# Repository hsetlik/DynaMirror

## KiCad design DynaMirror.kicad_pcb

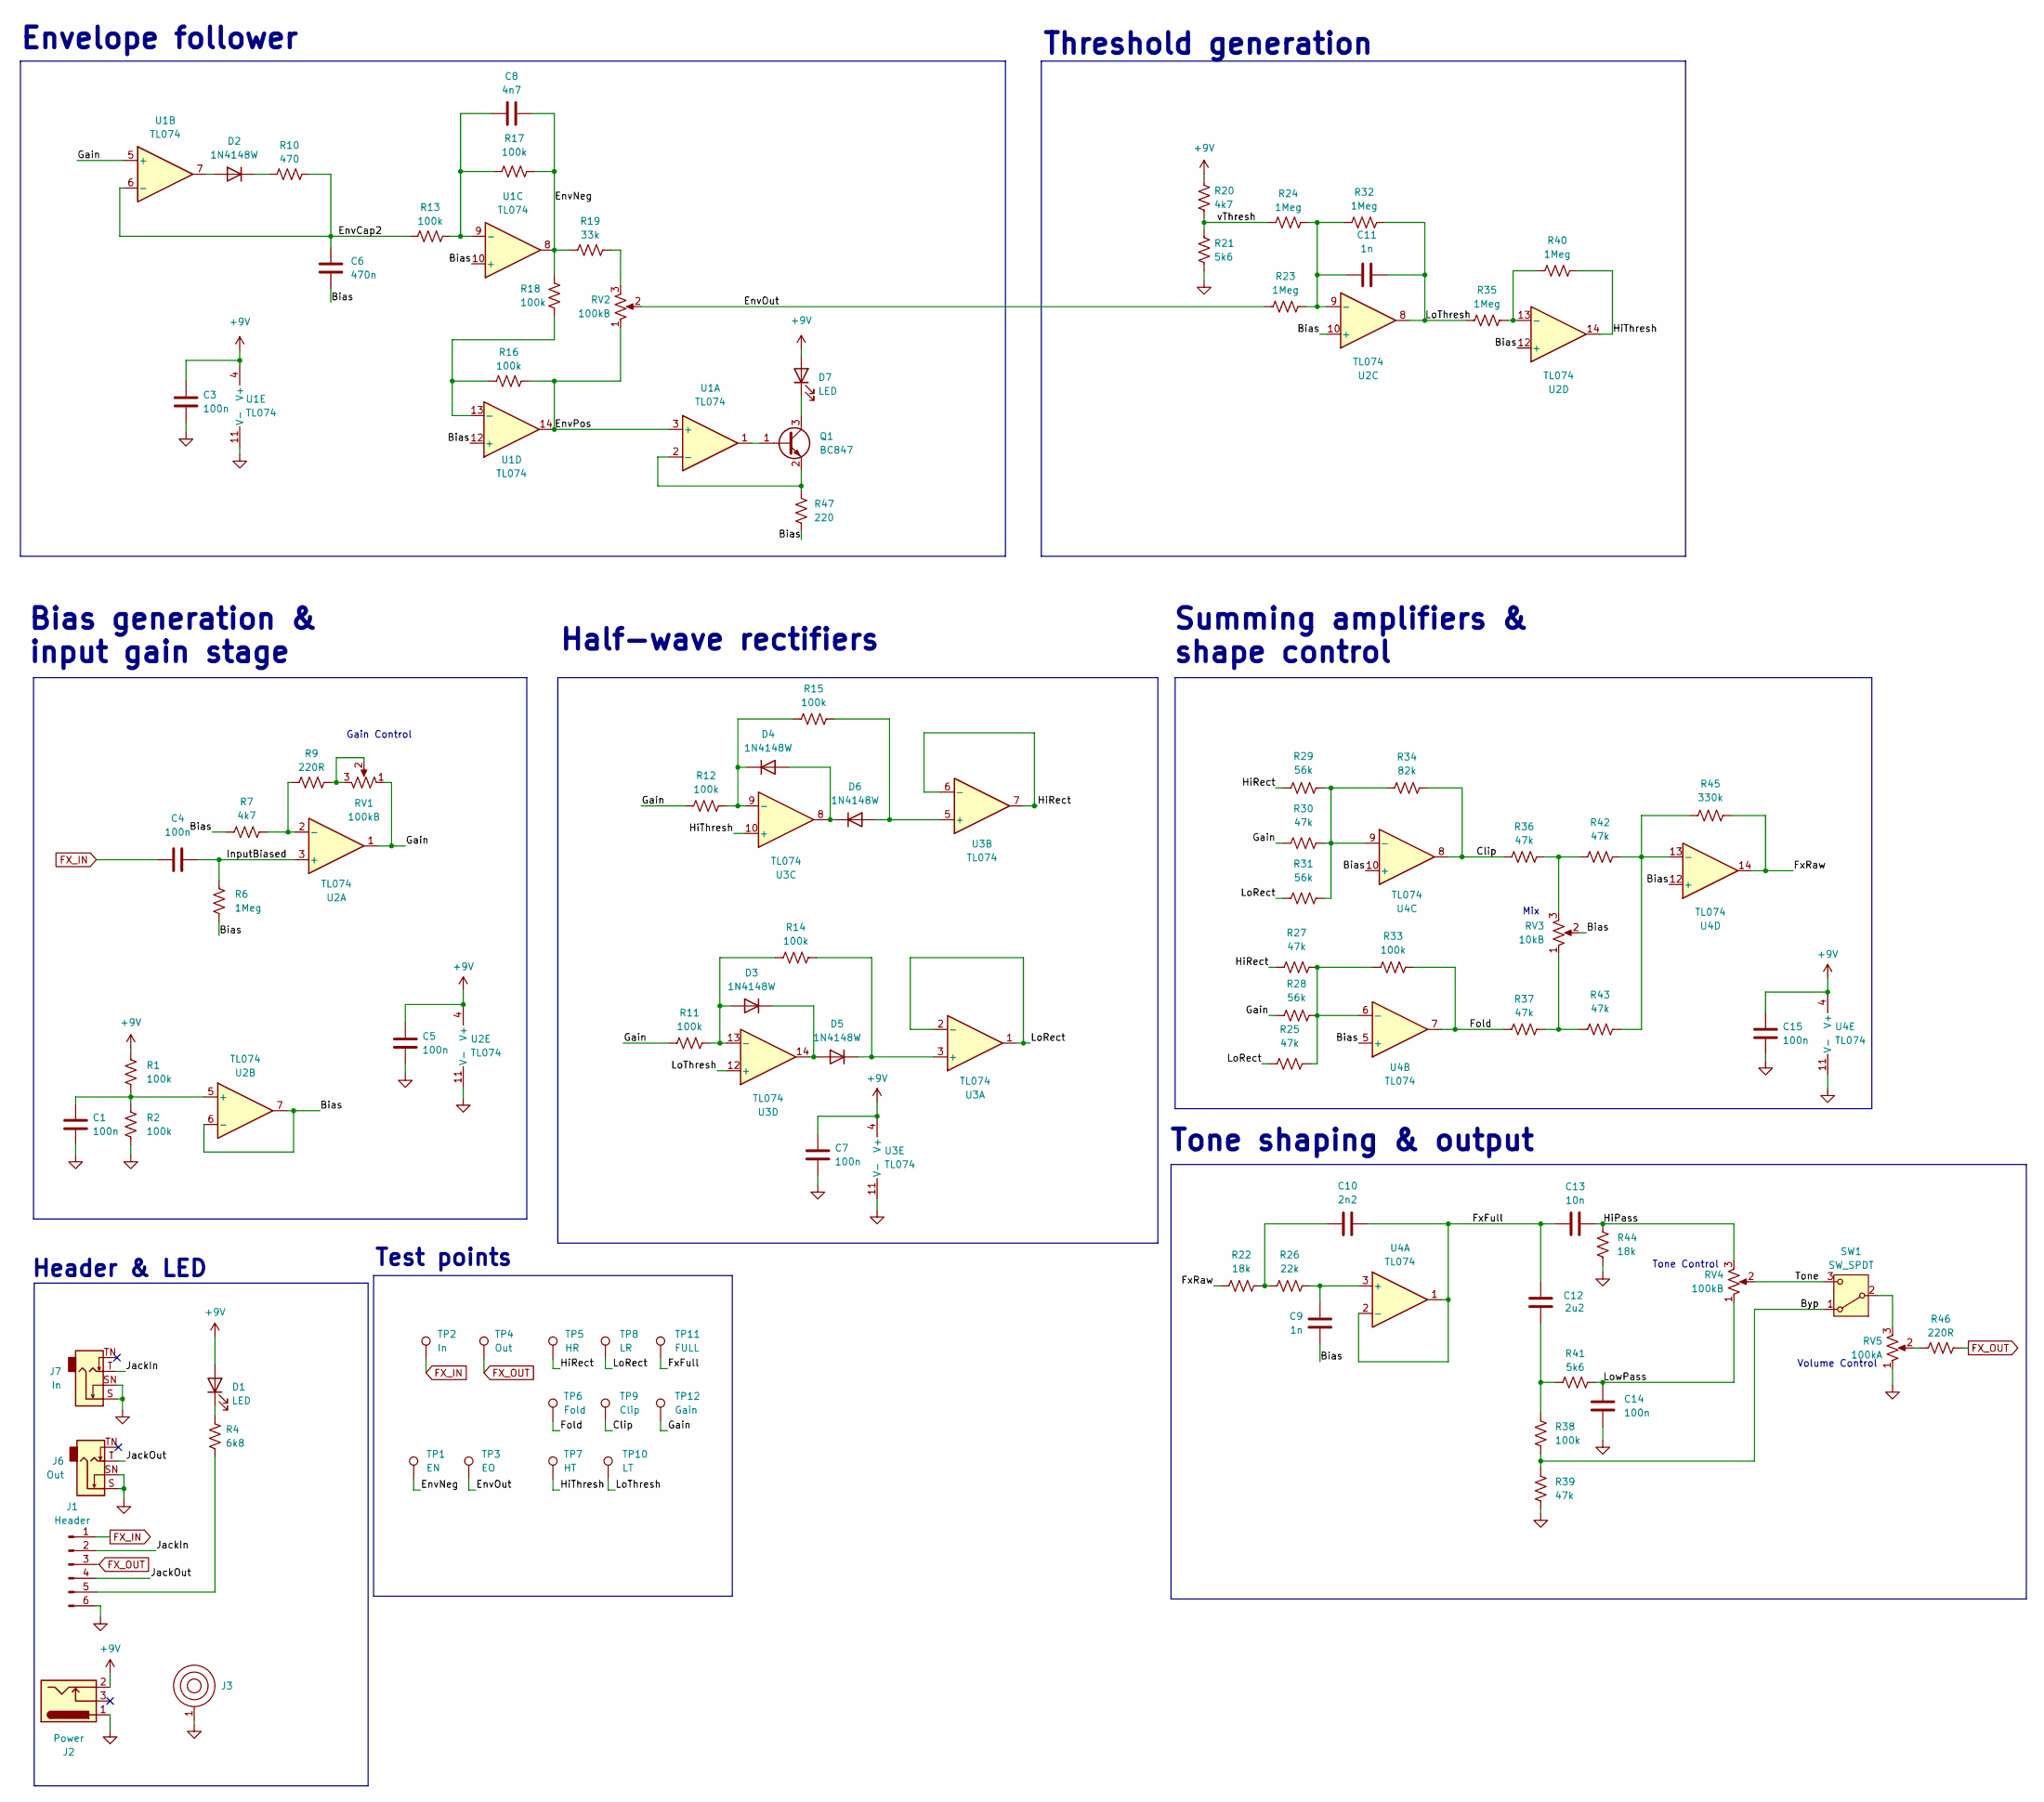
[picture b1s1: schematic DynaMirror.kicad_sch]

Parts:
C1, C3, C4, C5, C7, C14, C15: 100n; C_0805_2012Metric
C6: 470n; C_0805_2012Metric
C8: 4n7; C_0805_2012Metric
C9, C11: 1n; C_0805_2012Metric
C10: 2n2; C_0805_2012Metric
C12: 2u2; C_0805_2012Metric
C13: 10n; C_0805_2012Metric
D1, D7: LED; LED_D3.0mm
D2, D3, D4, D5, D6: 1N4148W; D_SOD-123
J1: Header; PinHeader_1x06_P2.54mm_Vertical
J2: Power; BarrelJack_Horizontal
J3: BatteryContact_Keystone_243
J6: Out; Jack_6.35mm_Tayda_PJ664C_Mono_Horizontal; MPN PJ-644C MONO
J7: In; Jack_6.35mm_Tayda_PJ664C_Mono_Horizontal; MPN PJ-644C MONO
Q1: BC847; SOT-23
R1, R2, R11, R12, R13, R14, R15, R16, R17, R18, R33, R38: 100k; R_0805_2012Metric
R4: 6k8; R_0805_2012Metric
R6, R23, R24, R32, R35, R40: 1Meg; R_0805_2012Metric
R7, R20: 4k7; R_0805_2012Metric
R9, R46: 220R; R_0805_2012Metric
R10: 470; R_0805_2012Metric
R19: 33k; R_0805_2012Metric
R21, R41: 5k6; R_0805_2012Metric
R22, R44: 18k; R_0805_2012Metric
R25, R27, R30, R36, R37, R39, R42, R43: 47k; R_0805_2012Metric
R26: 22k; R_0805_2012Metric
R28, R29, R31: 56k; R_0805_2012Metric
R34: 82k; R_0805_2012Metric
R45: 330k; R_0805_2012Metric
R47: 220; R_0805_2012Metric
RV1, RV2, RV4: 100kB; Potentiometer_Alpha_RV16AF_42_VeryLong
RV3: 10kB; Potentiometer_Alpha_RV16AF_42_VeryLong
RV5: 100kA; Potentiometer_Alpha_RV16AF_42_VeryLong
SW1: SW_SPDT; SW_SPDT_Dailywell_Mini_1M
TP1: EN; TestPoint_THTPad_D2.0mm_Drill1.0mm_VAL
TP2: In; TestPoint_THTPad_D2.0mm_Drill1.0mm_VAL
TP3: EO; TestPoint_THTPad_D2.0mm_Drill1.0mm_VAL
TP4: Out; TestPoint_THTPad_D2.0mm_Drill1.0mm_VAL
TP5: HR; TestPoint_THTPad_D2.0mm_Drill1.0mm_VAL
TP6: Fold; TestPoint_THTPad_D2.0mm_Drill1.0mm_VAL
TP7: HT; TestPoint_THTPad_D2.0mm_Drill1.0mm_VAL
TP8: LR; TestPoint_THTPad_D2.0mm_Drill1.0mm_VAL
TP9: Clip; TestPoint_THTPad_D2.0mm_Drill1.0mm_VAL
TP10: LT; TestPoint_THTPad_D2.0mm_Drill1.0mm_VAL
TP11: FULL; TestPoint_THTPad_D2.0mm_Drill1.0mm_VAL
TP12: Gain; TestPoint_THTPad_D2.0mm_Drill1.0mm_VAL
U1, U2, U3, U4: TL074; SOIC-14_3.9x8.7mm_P1.27mm

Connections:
+9V: C3.1, C5.1, C7.1, C15.1, D1.2 (A), D7.2 (A), J2.2, R1.1, R20.1, U1.4 (V+), U2.4 (V+), U3.4 (V+), U4.4 (V+)
/Bias: C6.2, C9.2, R6.2, R7.1, R47.2, RV3.2, U1.10 (+), U1.12 (+), U2.6 (-), U2.7, U2.10 (+), U2.12 (+), U4.5 (+), U4.10 (+), U4.12 (+)
/Byp: R38.2, R39.1, SW1.1 (A)
/Clip: R34.2, R36.1, TP9.1 (1_1), U4.8
/EnvCap2: C6.1, R10.2, R13.1, U1.6 (-)
/EnvNeg: C8.2, R17.2, R18.2, R19.2, TP1.1 (1_1), U1.8
/EnvOut: R23.2, RV2.2, TP3.1 (1_1)
/EnvPos: R16.1, RV2.1, U1.3 (+), U1.14
/Fold: R33.2, R37.1, TP6.1 (1_1), U4.7
/FxFull: C10.2, C12.1, C13.1, TP11.1 (1_1), U4.1, U4.2 (-)
/FxRaw: R22.1, R45.2, U4.14
/Gain: R11.1, R12.1, R28.1, R30.1, RV1.1, TP12.1 (1_1), U1.5 (+), U2.1
/HiPass: C13.2, R44.1, RV4.3
/HiRect: R27.1, R29.1, TP5.1 (1_1), U3.6 (-), U3.7
/HiThresh: R40.1, TP7.1 (1_1), U2.14, U3.10 (+)
/InputBiased: C4.2, R6.1, U2.3 (+)
/JackIn: J1.2, J7.T
/JackOut: J1.4, J6.T
/LoRect: R25.1, R31.1, TP8.1 (1_1), U3.1, U3.2 (-)
/LoThresh: C11.2, R32.1, R35.2, TP10.1 (1_1), U2.8, U3.12 (+)
/LowPass: C14.1, R41.2, RV4.1
/Tone: RV4.2, SW1.3 (C)
/vThresh: R20.2, R21.1, R24.2
FX_IN: C4.1, J1.1, TP2.1 (1_1)
FX_OUT: J1.3, R46.2, TP4.1 (1_1)
GND: C1.2, C3.2, C5.2, C7.2, C14.2, C15.2, J1.6, J2.1, J3.1, J6.S, J6.SN, J7.S, J7.SN, R2.2, R21.2, R39.2, R44.2, RV5.1, U1.11 (V-), U2.11 (V-), U3.11 (V-), U4.11 (V-)
unnamed: C10.1, R22.2, R26.1
unnamed: C12.2, R38.1, R41.1
unnamed: D1.1 (K), R4.1
unnamed: D2.2 (A), U1.7
unnamed: D2.1 (K), R10.1
unnamed: D3.2 (A), R11.2, R14.1, U3.13 (-)
unnamed: D3.1 (K), D5.2 (A), U3.14
unnamed: D4.2 (A), D6.1 (K), U3.8
unnamed: D4.1 (K), R12.2, R15.1, U3.9 (-)
unnamed: D5.1 (K), R14.2, U3.3 (+)
unnamed: D6.2 (A), R15.2, U3.5 (+)
unnamed: D7.1 (K), Q1.3 (C)
unnamed: J1.5, R4.2
unnamed: Q1.1 (B), U1.1
unnamed: Q1.2 (E), R47.1, U1.2 (-)
unnamed: R9.2, RV1.2, RV1.3
unnamed: R19.1, RV2.3
unnamed: R36.2, R42.1, RV3.3
unnamed: R37.2, R43.1, RV3.1
unnamed: R46.1, RV5.2
unnamed: RV5.3, SW1.2 (B)
unnamed: C8.1, R13.2, R17.1, U1.9 (-)
unnamed: R16.2, R18.1, U1.13 (-)
unnamed: R7.2, R9.1, U2.2 (-)
unnamed: C1.1, R1.2, R2.1, U2.5 (+)
unnamed: C11.1, R23.1, R24.1, R32.2, U2.9 (-)
unnamed: R35.1, R40.2, U2.13 (-)
unnamed: C9.1, R26.2, U4.3 (+)
unnamed: R25.2, R27.2, R28.2, R33.1, U4.6 (-)
unnamed: R29.2, R30.2, R31.2, R34.1, U4.9 (-)
unnamed: R42.2, R43.2, R45.1, U4.13 (-)

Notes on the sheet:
Threshold generation
Summing amplifiers & shape control
Tone shaping & output
Gain Control
Bias generation & input gain stage
Envelope follower
Volume Control
Mix
Test points
Half-wave rectifiers
Header & LED
Tone Control

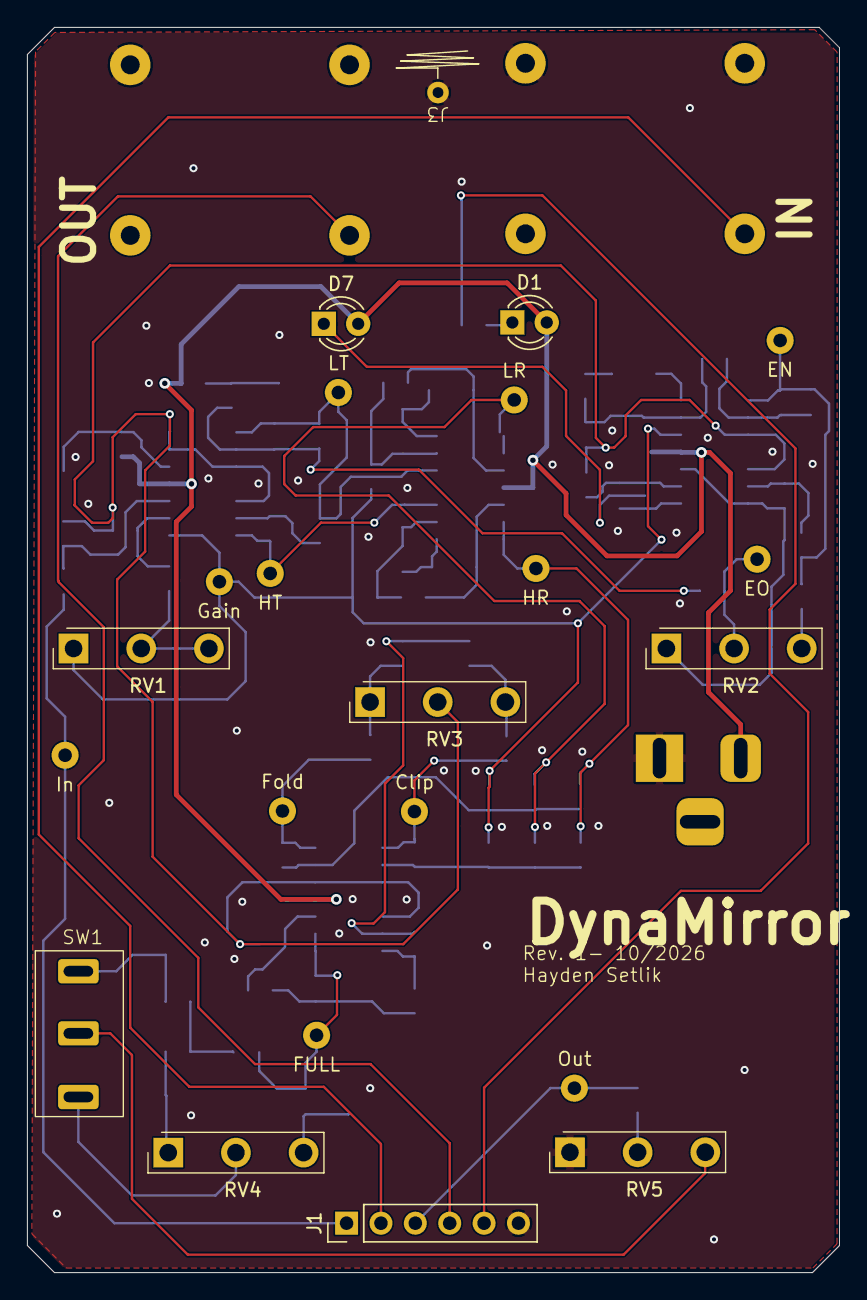
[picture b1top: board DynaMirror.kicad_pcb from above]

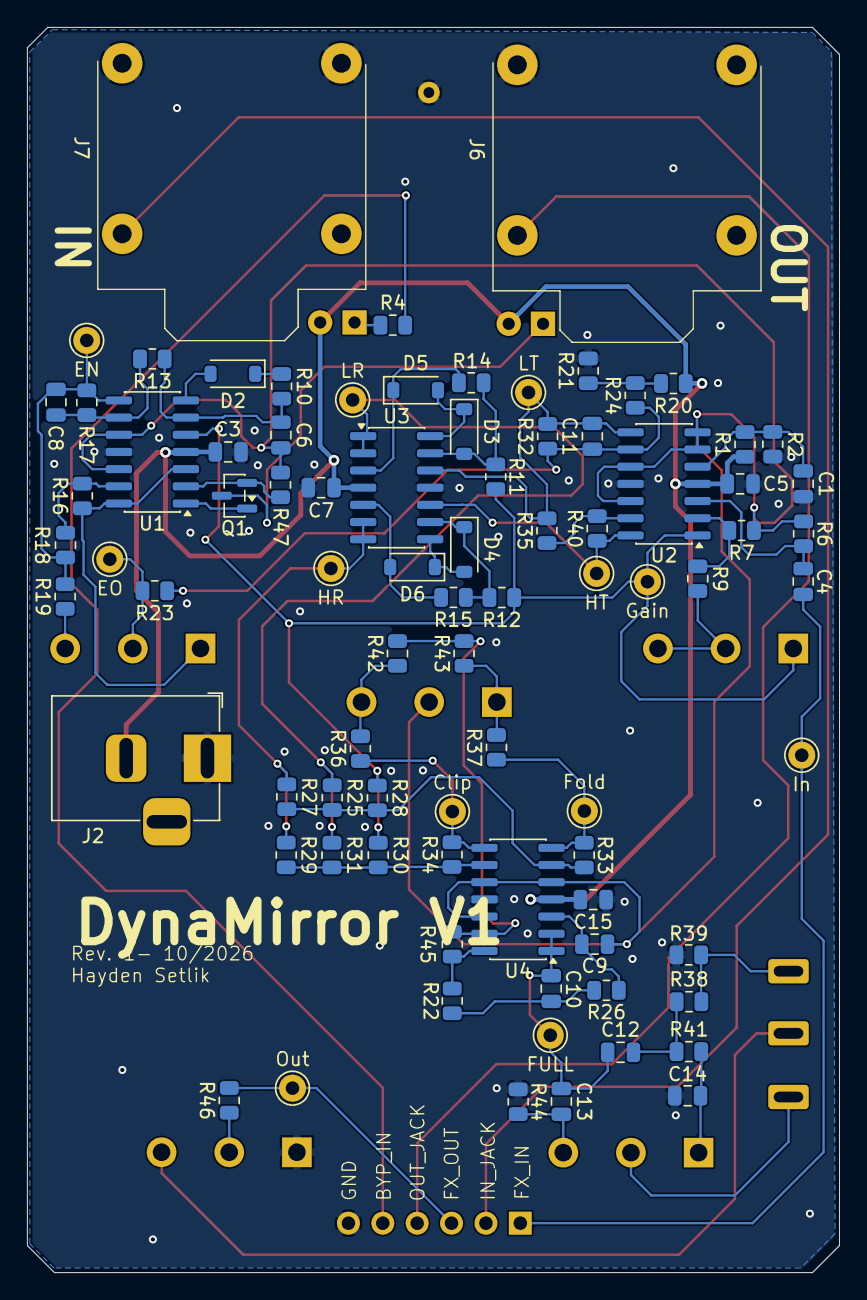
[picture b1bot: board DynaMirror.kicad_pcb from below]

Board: 2 copper layers, 60.0 x 92.0 mm, 93 parts (83 on the bottom side), 57 nets.

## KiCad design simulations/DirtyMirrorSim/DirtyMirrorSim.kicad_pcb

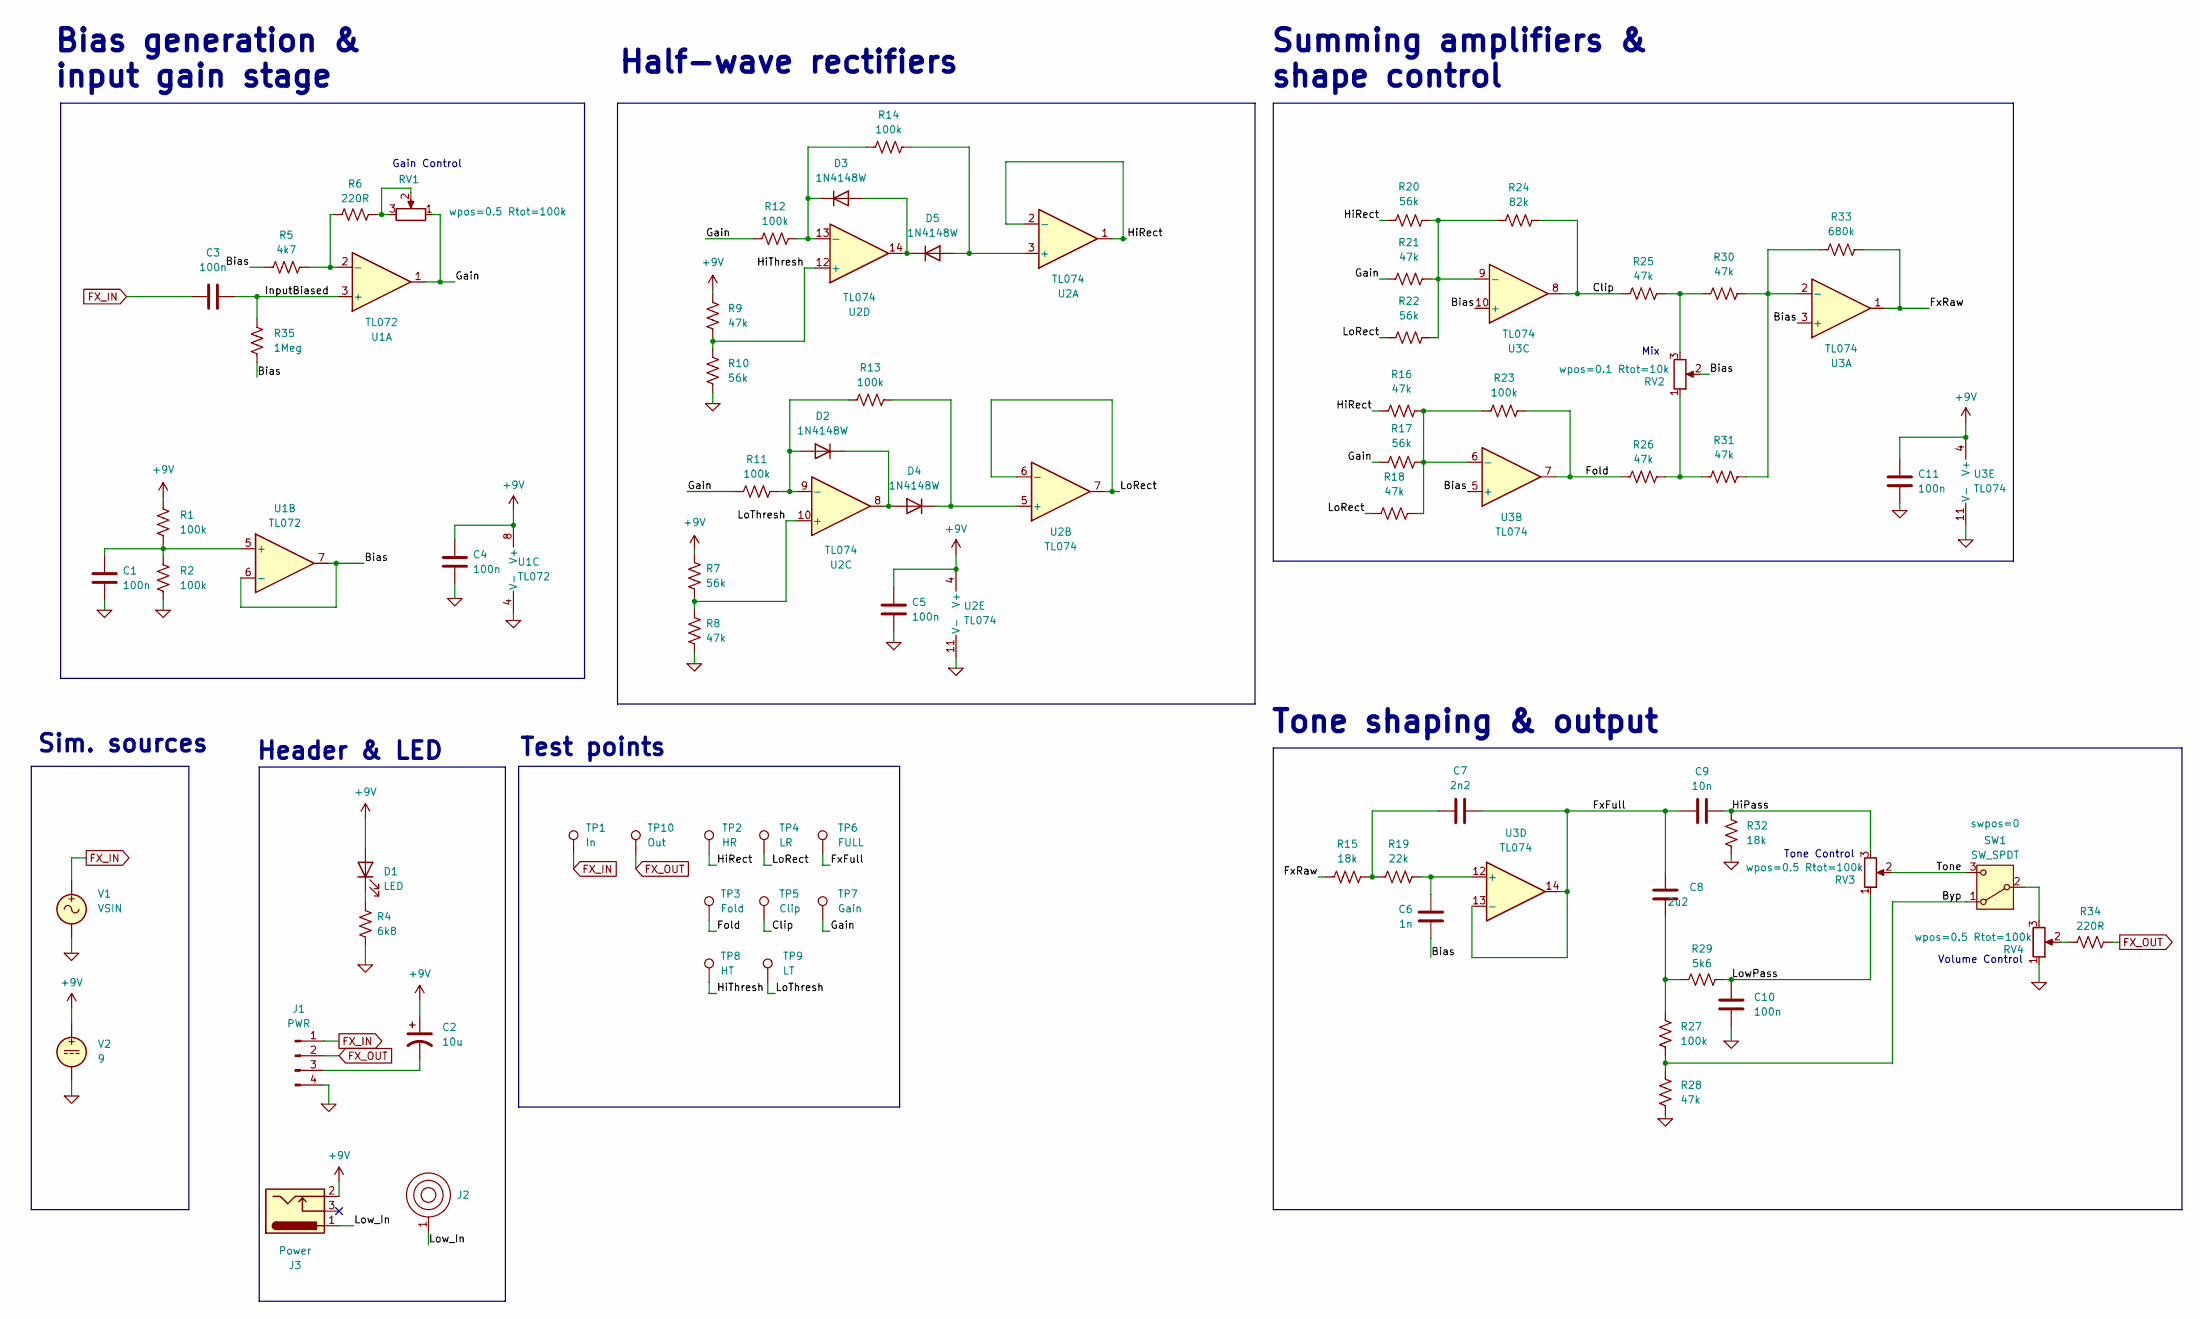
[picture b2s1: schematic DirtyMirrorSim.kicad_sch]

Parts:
C1, C3, C4, C5, C10, C11: 100n; C_0805_2012Metric
C2: 10u; CP_Radial_D5.0mm_P2.50mm
C6: 1n; C_0805_2012Metric
C7: 2n2; C_0805_2012Metric
C8: 2u2; C_0805_2012Metric
C9: 10n; C_0805_2012Metric
D1: LED; LED_D3.0mm
D2, D3, D4, D5: 1N4148W; D_SOD-123
J1: PWR; PinHeader_1x04_P2.54mm_Vertical
J2: BatteryContact_Keystone_243
J3: Power; BarrelJack_Horizontal
R1, R2, R11, R12, R13, R14, R23, R27: 100k; R_0805_2012Metric
R4: 6k8; R_0805_2012Metric
R5: 4k7; R_0805_2012Metric
R6, R34: 220R; R_0805_2012Metric
R7, R10, R17, R20, R22: 56k; R_0805_2012Metric
R8, R9, R16, R18, R21, R25, R26, R28, R30, R31: 47k; R_0805_2012Metric
R15, R32: 18k; R_0805_2012Metric
R19: 22k; R_0805_2012Metric
R24: 82k; R_0805_2012Metric
R29: 5k6; R_0805_2012Metric
R33: 680k; R_0805_2012Metric
R35: 1Meg; R_0805_2012Metric
RV1, RV2, RV3, RV4: R_Potentiometer; Potentiometer_Alpha_RV16AF_42_Single_Long
SW1: SW_SPDT; Toggle_Dailywell_SubMini_SPDT
TP1: In; TestPoint_THTPad_D2.0mm_Drill1.0mm_VAL
TP2: HR; TestPoint_THTPad_D2.0mm_Drill1.0mm_VAL
TP3: Fold; TestPoint_THTPad_D2.0mm_Drill1.0mm_VAL
TP4: LR; TestPoint_THTPad_D2.0mm_Drill1.0mm_VAL
TP5: Clip; TestPoint_THTPad_D2.0mm_Drill1.0mm_VAL
TP6: FULL; TestPoint_THTPad_D2.0mm_Drill1.0mm_VAL
TP7: Gain; TestPoint_THTPad_D2.0mm_Drill1.0mm_VAL
TP8: HT; TestPoint_THTPad_D2.0mm_Drill1.0mm_VAL
TP9: LT; TestPoint_THTPad_D2.0mm_Drill1.0mm_VAL
TP10: Out; TestPoint_THTPad_D2.0mm_Drill1.0mm_VAL
U1: TL072; SOIC-8_3.9x4.9mm_P1.27mm
U2, U3: TL074; SOIC-14_3.9x8.7mm_P1.27mm
V1: VSIN
V2: 9

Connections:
+9V: C2.1, C4.1, C5.1, C11.1, D1.2 (A), J3.2, R1.1, R7.1, R9.1, U1.8 (V+), U2.4 (V+), U3.4 (V+), V2.1
/Bias: C6.2, R5.1, R35.2, RV2.2, U1.6 (-), U1.7, U3.3 (+), U3.5 (+), U3.10 (+)
/Byp: R27.2, R28.1, SW1.1 (A)
/Clip: R24.2, R25.1, TP5.1 (1_1), U3.8
/Fold: R23.2, R26.1, TP3.1 (1_1), U3.7
/FxFull: C7.2, C8.1, C9.1, TP6.1 (1_1), U3.13 (-), U3.14
/FxRaw: R15.1, R33.2, U3.1
/Gain: R11.1, R12.1, R17.1, R21.1, RV1.1, TP7.1 (1_1), U1.1
/HiPass: C9.2, R32.1, RV3.3
/HiRect: R16.1, R20.1, TP2.1 (1_1), U2.1, U2.2 (-)
/HiThresh: R9.2, R10.1, TP8.1 (1_1), U2.12 (+)
/InputBiased: C3.2, R35.1, U1.3 (+)
/LoRect: R18.1, R22.1, TP4.1 (1_1), U2.6 (-), U2.7
/LoThresh: R7.2, R8.1, TP9.1 (1_1), U2.10 (+)
/LowPass: C10.1, R29.2, RV3.1
/Tone: RV3.2, SW1.3 (C)
FX_IN: C3.1, J1.1, TP1.1 (1_1), V1.1; also elsewhere on the board
FX_OUT: J1.2, R34.2, TP10.1 (1_1)
unnamed: C7.1, R15.2, R19.1
unnamed: C8.2, R27.1, R29.1
unnamed: D1.1 (K), R4.1
unnamed: D2.2 (A), R11.2, R13.1, U2.9 (-)
unnamed: D2.1 (K), D4.2 (A), U2.8
unnamed: D3.2 (A), D5.1 (K), U2.14
unnamed: D3.1 (K), R12.2, R14.1, U2.13 (-)
unnamed: D4.1 (K), R13.2, U2.5 (+)
unnamed: D5.2 (A), R14.2, U2.3 (+)
unnamed: R6.2, RV1.2, RV1.3
unnamed: R25.2, R30.1, RV2.3
unnamed: R26.2, R31.1, RV2.1
unnamed: R34.1, RV4.2
unnamed: RV4.3, SW1.2 (B)
unnamed: R5.2, R6.1, U1.2 (-)
unnamed: C1.1, R1.2, R2.1, U1.5 (+)
unnamed: R30.2, R31.2, R33.1, U3.2 (-)
unnamed: R16.2, R17.2, R18.2, R23.1, U3.6 (-)
unnamed: R20.2, R21.2, R22.2, R24.1, U3.9 (-)
unnamed: C6.1, R19.2, U3.12 (+)

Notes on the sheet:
Test points
Gain Control
Sim. sources
Header & LED
Tone Control
Summing amplifiers & shape control
Mix
Bias generation & input gain stage
Volume Control
Half-wave rectifiers
Tone shaping & output

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
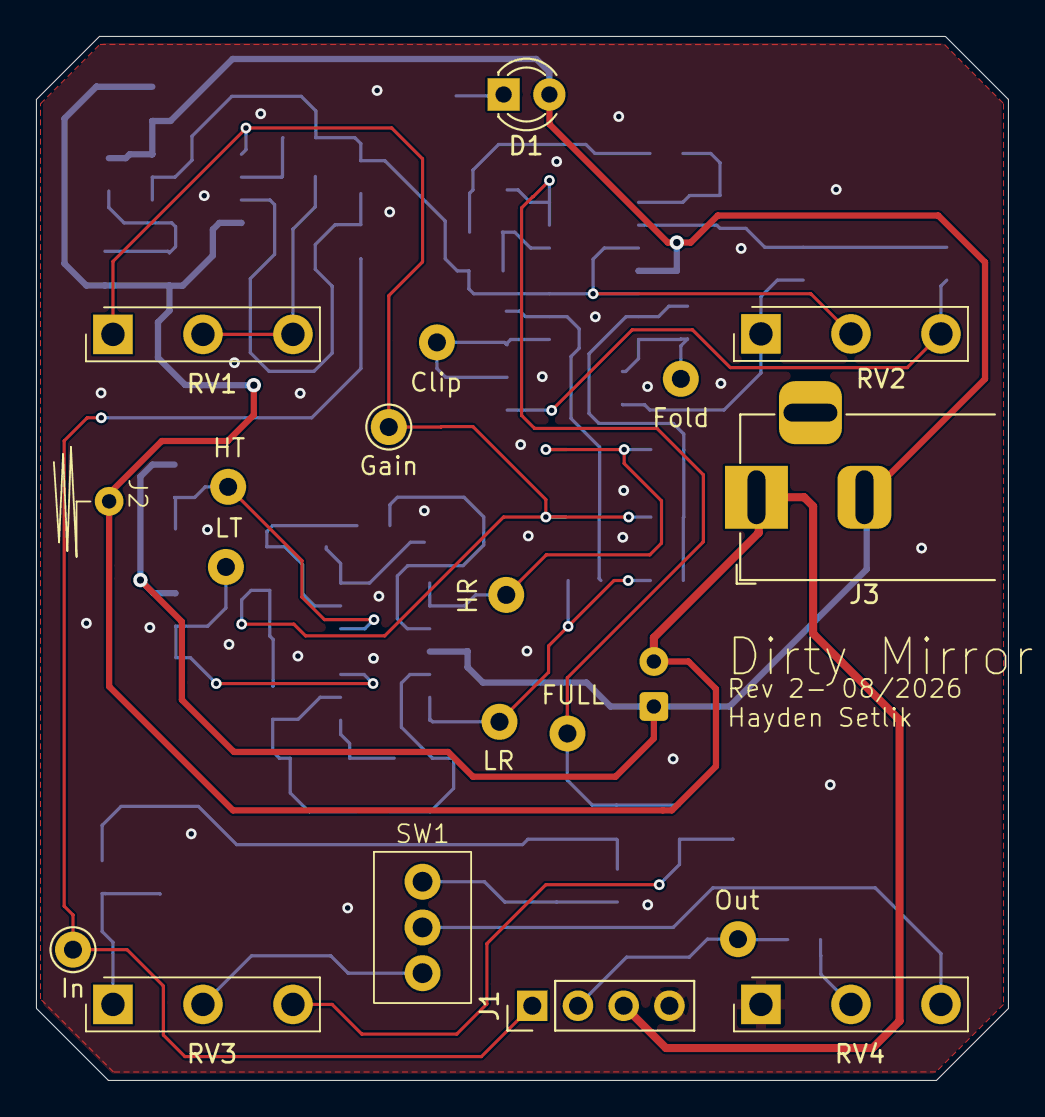
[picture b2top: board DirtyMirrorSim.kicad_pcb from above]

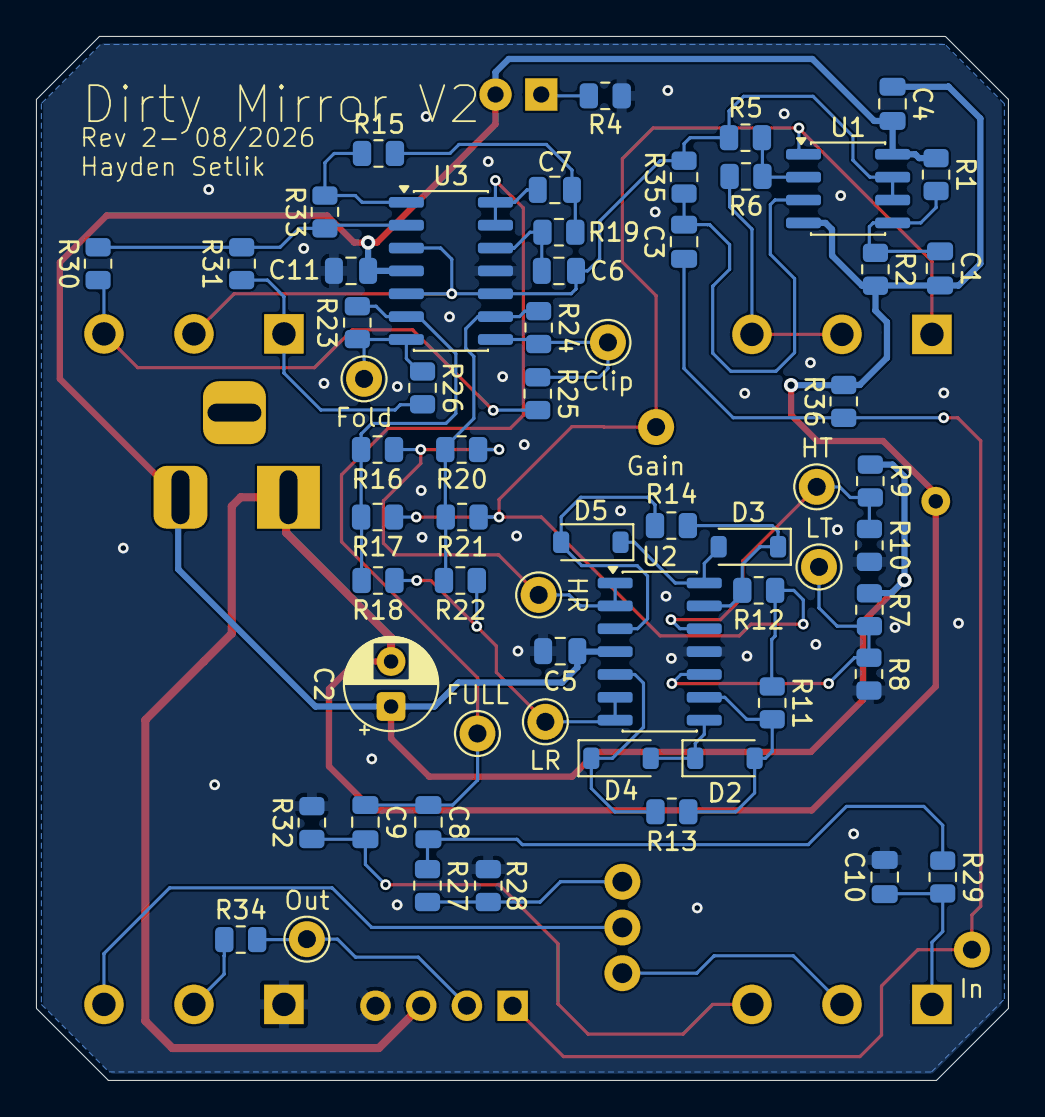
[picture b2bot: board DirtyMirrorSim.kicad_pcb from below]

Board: 2 copper layers, 54.0 x 58.0 mm, 72 parts (61 on the bottom side), 40 nets.

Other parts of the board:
R36: 1Meg; R_0805_2012Metric

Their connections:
FX_IN: R36.1; also elsewhere on the board
